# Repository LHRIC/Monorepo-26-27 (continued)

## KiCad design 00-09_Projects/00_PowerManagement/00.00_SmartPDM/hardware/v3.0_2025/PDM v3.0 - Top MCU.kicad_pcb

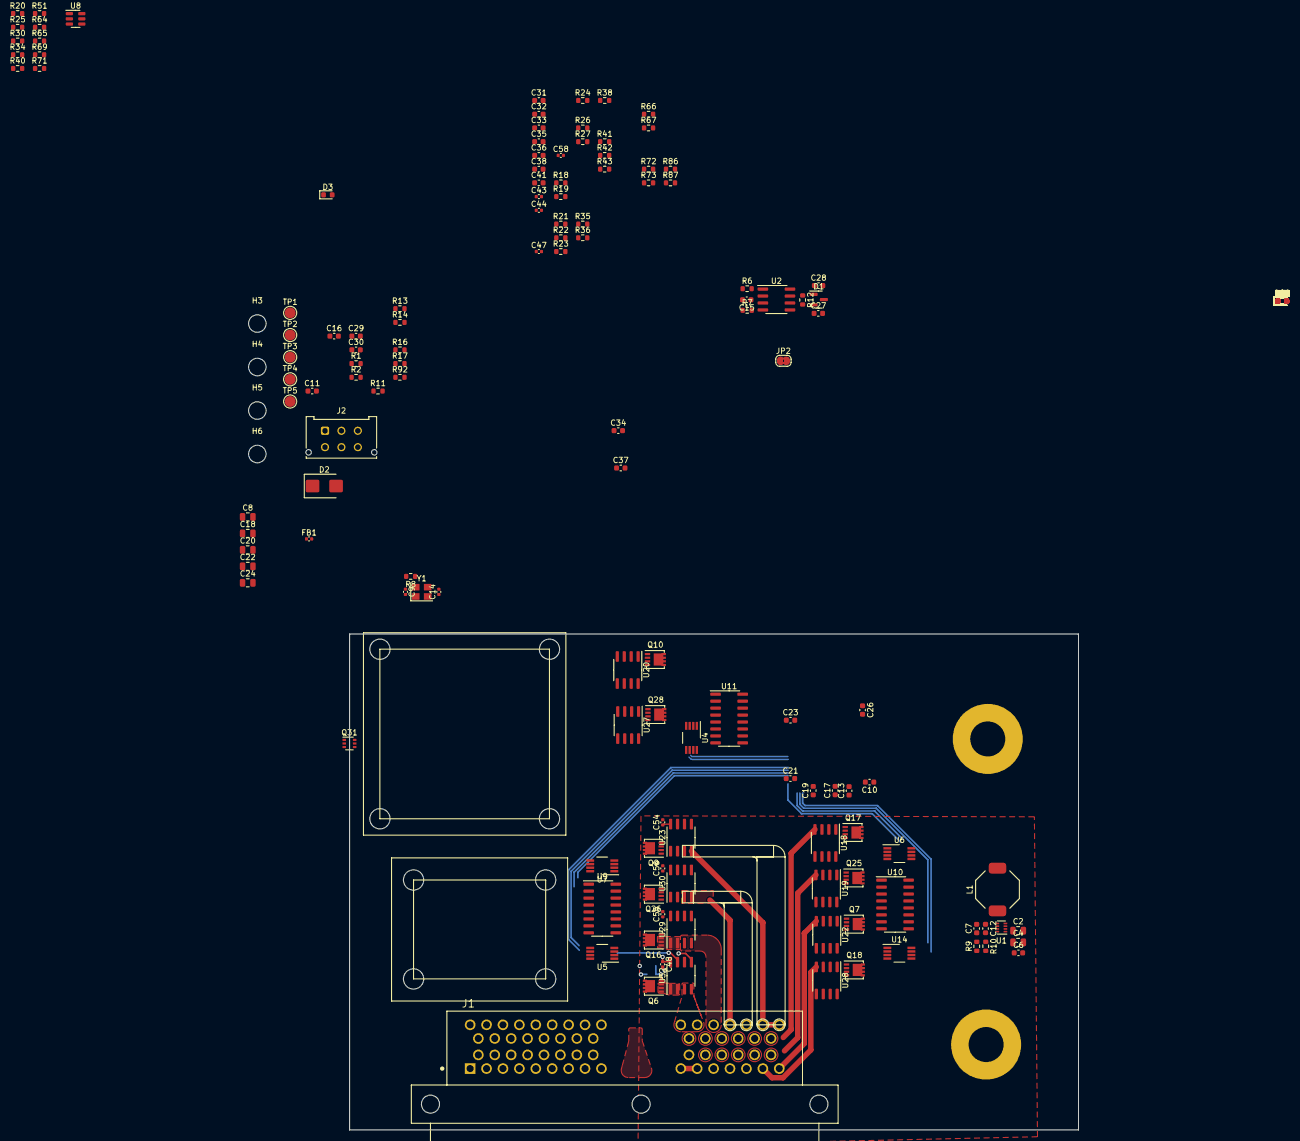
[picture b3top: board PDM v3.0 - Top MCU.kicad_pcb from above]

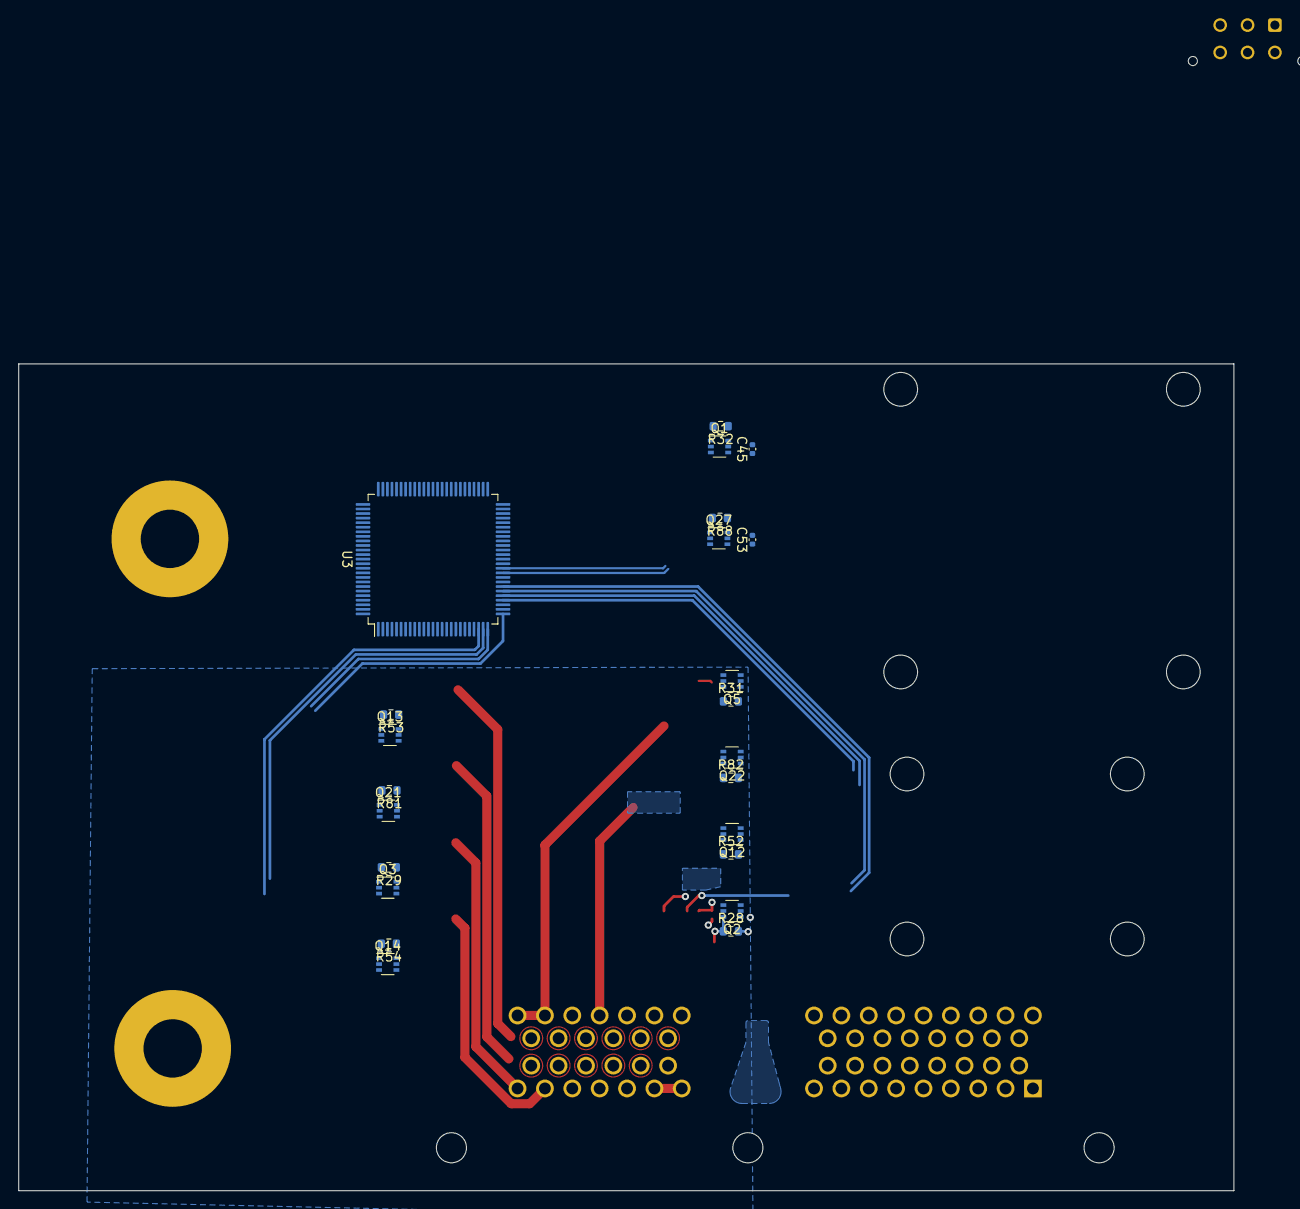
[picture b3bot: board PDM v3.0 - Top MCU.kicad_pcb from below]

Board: 4 copper layers, 133.2 x 90.6 mm, 210 parts (23 on the bottom side), 155 nets.

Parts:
C2, C4: 4.7uF; C_0805_2012Metric
C6, C12, C31, C32, C33, C34, C35, C36, C37, C38, C41: .1uF; C_0603_1608Metric
C7: 33nF; C_0603_1608Metric
C8: 10uF; C_0805_2012Metric
C9, C14: 12pF; C_0402_1005Metric
C10, C11, C13, C15, C17, C19, C21, C23, C26: 0.1uF; C_0603_1608Metric
C16: 1uF; C_0603_1608Metric
C18: C_Small; C_0805_2012Metric
C20, C22, C24: 22uF; C_0805_2012Metric
C27, C28: 100pF; C_0603_1608Metric
C29, C30: 2.2uF; C_0603_1608Metric
C43, C44, C45, C47, C48, C53, C54, C55, C56, C58: .1uF; C_0402_1005Metric
D1: D_TVS_Dual_AAC; SOT-23
D2: 33.2v; D_SMB
D3, D4, D6, D8, D10, D12, D14, D16, D18, D20, D22: RED; LED_0603_1608Metric
D5, D7, D9, D11, D13, D15, D17, D19, D21, D23: GREEN; LED_0603_1608Metric
FB1: 100 @ 100MHz; C_0402_1005Metric
H1, H2: SurLok; SurLok_5.7
H3, H4, H5, H6: Hole; MountingHole_3.2mm_M3
H7, H8, H9, H10, H11, H12, H13, H14: Hole; MountingHole_3.7mm
J1: Conn_02x30; TE_6473427-1
J2: Conn_02x03_Odd_Even; Molex_Micro-Fit_3.0_43045-0612_2x03_P3.00mm_Vertical
JP2: Jumper_2_Bridged; SolderJumper-2_P1.3mm_Bridged2Bar_RoundedPad1.0x1.5mm
L1: 4.7uH; SRU8043-4R7Y
Q1, Q2, Q3, Q5, Q12, Q13, Q14, Q21, Q22, Q27: DMN63D8LDW; SOT-363_SC-70-6
Q6, Q7, Q9, Q10, Q16, Q17, Q18, Q25, Q26, Q28: SiS443DN; Vishay_PowerPAK_1212-8_Single
Q31: BSD235C; SOT-363_SC-70-6
R1: 16k; R_0603_1608Metric
R2: 3.9k; R_0603_1608Metric
R6, R7: 1k; R_0603_1608Metric
R8: 220; R_0603_1608Metric
R9: 30.9k; R_0603_1608Metric
R10, R13, R14, R17, R92: 10k; R_0603_1608Metric
R11, R18, R19, R20, R21, R22, R23, R24, R25, R26, R27, R30, R34, R35, R36, R38, R40, R41, R42, R43, R51, R64, R65, R66, R67, R69, R71, R72, R73, R86, R87: R_Small; R_0603_1608Metric
R12: 120; R_0603_1608Metric
R16, R33, R37, R39, R44, R45, R46, R47, R48, R49, R50, R55, R56, R57, R58, R59, R60, R61, R62, R63, R68: 330; R_0603_1608Metric
R28, R29, R31, R32, R52, R53, R54, R81, R82, R88: 100k; R_0603_1608Metric
TP1, TP2, TP3, TP4, TP5: TP; TestPoint_Pad_D2.0mm
U1: TPS62933; SOT-583
U2: SN65HVD230; SOIC-8_3.9x4.9mm_P1.27mm
U3: STM32F407VETx; LQFP-100_14x14mm_P0.5mm
U4, U5, U6, U7, U14: TLV7012DGKR; VSSOP-8_3.0x3.0mm_P0.65mm
U8: MAX6817EUT+T; SOT-23-6
U9, U10, U11: MC14043B; SOIC-16_3.9x9.9mm_P1.27mm
U18, U19, U20, U22, U23, U27, U28, U29, U30, U32: TMCS1108A3UQDR; SOIC-8_3.9x4.9mm_P1.27mm
Y1: 16MHz; Crystal_SMD_3225-4Pin_3.2x2.5mm

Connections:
+3.3VA: C11.1, C16.1, FB1.2, TP3.1, U3.21 (VREF+), U3.22 (VDDA)
+3V3: C8.1, C10.1, C13.1, C15.1, C17.1, C19.1, C20.1, C21.1, C22.1, C23.1, C24.1, C26.1, C31.1, C32.1, C33.1, C34.1, C35.1, C36.1, C37.1, C38.1, C41.1, C43.1, C44.1, C45.1, C47.1, C48.1, C53.1, C54.1, C55.1, C56.1, C58.1, FB1.1, J2.2, L1.2, R9.1, R13.1, R14.1, R16.1, R18.2, R19.2, R20.2, R21.2, R22.2, R25.2, R30.2, R34.2, R35.2, R36.2, R38.2, R40.2, R51.2, R64.2, R65.2, R66.2, R67.2, R69.2, R71.2, R86.2, R92.1, TP4.1, U2.3 (VCC), U3.6 (VBAT), U3.11 (VDD), U3.19 (VDD), U3.28 (VDD), U3.50 (VDD), U3.75 (VDD), U3.100 (VDD), U4.8 (V+), U5.8 (V+), U6.8 (V+), U7.8 (V+), U8.5 (VCC), U9.5 (Enable), U9.16 (V+), U10.5 (Enable), U10.16 (V+), U11.5 (Enable), U11.16 (V+), U14.8 (V+), U18.8 (VS), U19.8 (VS), U20.8 (VS), U22.8 (VS), U23.8 (VS), U27.8 (VS), U28.8 (VS), U29.8 (VS), U30.8 (VS), U32.8 (VS)
+12V: C2.1, C4.1, C6.1, C18.1, D2.2 (A2), H1.1, Q6.5 (D), Q7.5 (D), Q9.5 (D), Q10.5 (D), Q16.5 (D), Q17.5 (D), Q18.5 (D), Q25.5 (D), Q26.5 (D), Q28.5 (D), R1.1, R28.2, R29.2, R31.2, R32.2, R52.2, R53.2, R54.2, R81.2, R82.2, R88.2, TP1.1, U1.3 (VIN)
BSPD Switch: C18.2, R11.1
CAN_H: C27.1, D1.2 (A2), J1.26, R12.1, U2.7 (CANH)
CAN_L: C28.1, D1.1 (A1), J1.27, R12.2, U2.6 (CANL)
CAN_RX: R7.1, U3.70 (PA11)
CAN_SLEEP: U2.8 (Rs), U3.2 (PE3)
CAN_TX: R6.1, U3.71 (PA12)
CH1_CS: U3.32 (PA7), U5.6 (-), U32.7 (VOUT)
CH1_EN: Q2.2 (G), R20.1, U3.62 (PD15)
CH1_Fault: Q2.5 (G), U3.33 (PC4), U9.2 (Q)
CH1_OUT: J1.54, J1.55, U32.3 (IN-), U32.4 (IN-)
CH1_R: U3.51 (PB12), U9.4 (S)
CH2_CS: U3.31 (PA6), U5.2 (-), U29.7 (VOUT)
CH2_EN: Q12.2 (G), R40.1, U3.63 (PC6)
CH2_Fault: Q12.5 (G), U3.34 (PC5), U9.9 (Q)
CH2_OUT: J1.56, U29.3 (IN-), U29.4 (IN-)
CH2_R: U3.52 (PB13), U9.6 (S)
CH3_CS: U3.30 (PA5), U7.3 (+), U30.7 (VOUT)
CH3_EN: Q22.2 (G), R51.1, U3.64 (PC7)
CH3_Fault: Q22.5 (G), U3.37 (PB2), U9.1 (Q)
CH3_OUT: J1.57, J1.58, U30.3 (IN-), U30.4 (IN-)
CH3_R: U3.53 (PB14), U9.14 (S)
CH4_CS: U3.29 (PA4), U7.6 (-), U23.7 (VOUT)
CH4_EN: Q5.2 (G), R71.1, U3.65 (PC8)
CH4_Fault: Q5.5 (G), U3.38 (PE7), U9.10 (Q)
CH4_OUT: J1.59, J1.60, U23.3 (IN-), U23.4 (IN-)
CH4_R: U3.54 (PB15), U9.12 (S)
CH5_CS: U3.26 (PA3), U14.3 (+), U18.7 (VOUT)
CH5_EN: Q13.2 (G), R25.1, U3.66 (PC9)
CH5_Fault: Q13.5 (G), U3.39 (PE8), U10.2 (Q)
CH5_OUT: J1.53, U18.3 (IN-), U18.4 (IN-)
CH5_R: U3.55 (PD8), U10.4 (S)
CH6_CS: U3.25 (PA2), U14.6 (-), U19.7 (VOUT)
CH6_EN: Q21.2 (G), R34.1, U3.67 (PA8)
CH6_Fault: Q21.5 (G), U3.40 (PE9), U10.9 (Q)
CH6_OUT: J1.47, U19.3 (IN-), U19.4 (IN-)
CH6_R: U3.56 (PD9), U10.6 (S)
CH7_CS: U3.24 (PA1), U6.3 (+), U22.7 (VOUT)
CH7_EN: Q3.2 (G), R64.1, U3.68 (PA9)
CH7_Fault: Q3.5 (G), U3.41 (PE10), U10.10 (Q)
CH7_OUT: J1.41, U22.3 (IN-), U22.4 (IN-)
CH7_R: U3.57 (PD10), U10.12 (S)
CH8_CS: U3.23 (PA0), U6.5 (+), U28.7 (VOUT)
CH8_EN: Q14.2 (G), R69.1, U3.69 (PA10)
CH8_Fault: Q14.5 (G), U3.42 (PE11), U10.1 (Q)
CH8_OUT: J1.40, U28.3 (IN-), U28.4 (IN-)
CH8_R: U3.58 (PD11), U10.14 (S)
CH9_CS: U3.35 (PB0), U4.3 (+), U20.7 (VOUT)
CH9_EN: Q1.2 (G), R30.1, U3.46 (PE15)
CH9_Fault: Q1.5 (G), U3.43 (PE12), U11.2 (Q)
CH9_OUT: U20.3 (IN-), U20.4 (IN-)
CH9_R: U3.59 (PD12), U11.4 (S)
CH10_CS: U3.36 (PB1), U4.6 (-), U27.7 (VOUT)
CH10_EN: Q27.2 (G), R65.1, U3.47 (PB10)
CH10_Fault: Q27.5 (G), U3.44 (PE13), U11.9 (Q)
CH10_OUT: U27.3 (IN-), U27.4 (IN-)
CH10_R: U3.60 (PD13), U11.6 (S)
GND: C2.2, C4.2, C6.2, C7.2, C8.2, C9.1, C10.2, C11.2, C13.2, C14.1, C15.2, C16.2, C17.2, C19.2, C20.2, C21.2, C22.2, C23.2, C24.2, C26.2, C27.2, C28.2, C29.1, C30.1, C31.2, C32.2, C33.2, C34.2, C35.2, C36.2, C37.2, C38.2, C41.2, C43.2, C44.2, C45.2, C47.2, C48.2, C53.2, C54.2, C55.2, C56.2, C58.2, D1.3 (common), D2.1 (A1), D3.1 (K), D4.1 (K), D5.1 (K), D6.1 (K), D7.1 (K), D8.1 (K), D9.1 (K), D10.1 (K), D11.1 (K), D12.1 (K), D13.1 (K), D14.1 (K), D15.1 (K), D16.1 (K), D17.1 (K), D18.1 (K), D19.1 (K), D20.1 (K), D21.1 (K), D22.1 (K), D23.1 (K), H2.1, J1.37, J1.38, J1.39, J1.43, J1.44, J1.45, J1.46, J1.49, J1.50, J1.51, J1.52, J2.5, JP2.2 (B), Q1.1 (S), Q2.1 (S), Q3.1 (S), Q5.1 (S), Q12.1 (S), Q13.1 (S), Q14.1 (S), Q21.1 (S), Q22.1 (S), Q27.1 (S), Q31.1 (SN), Q31.3 (DP), R2.2, R10.2, R11.2, R17.1, R23.2, R24.2, R26.2, R27.2, R41.2, R42.2, R43.2, R72.2, R73.2, R87.2, TP2.1, TP5.1, U1.4 (GND), U2.2 (GND), U3.10 (VSS), U3.20 (VSSA), U3.27 (VSS), U3.74 (VSS), U3.99 (VSS), U4.4 (V-), U5.4 (V-), U6.4 (V-), U7.4 (V-), U8.2 (GND), U9.8 (V-), U10.8 (V-), U11.8 (V-), U14.4 (V-), U18.5 (GND), U19.5 (GND), U20.5 (GND), U22.5 (GND), U23.5 (GND), U27.5 (GND), U28.5 (GND), U29.5 (GND), U30.5 (GND), U32.5 (GND), Y1.2, Y1.4
HSE_IN: C9.2, U3.12 (PH0), Y1.1
HSE_OUT: R8.2, U3.13 (PH1)
Key: R13.2, U8.1 (IN1)
Key_DB: U3.16 (PC1), U8.6 (OUT1)
NRST: J2.1, Q31.4 (SP), U3.14 (NRST)
unnamed: C14.2, R8.1, Y1.3
unnamed: D3.2 (A), R16.2
unnamed: D4.2 (A), R33.2
unnamed: D5.2 (A), R37.2
unnamed: D6.2 (A), R39.2
unnamed: D7.2 (A), R44.2
unnamed: D8.2 (A), R45.2
unnamed: D9.2 (A), R46.2
unnamed: D10.2 (A), R47.2
unnamed: D11.2 (A), R48.2
unnamed: D12.2 (A), R49.2
unnamed: D13.2 (A), R50.2
unnamed: D14.2 (A), R55.2
unnamed: D15.2 (A), R56.2
unnamed: D16.2 (A), R57.2
unnamed: D17.2 (A), R58.2
unnamed: D18.2 (A), R59.2
unnamed: D19.2 (A), R60.2
unnamed: D20.2 (A), R61.2
unnamed: D21.2 (A), R62.2
unnamed: D22.2 (A), R63.2
unnamed: D23.2 (A), R68.2
unnamed: J1.10, J1.11, J1.12, J1.13, J1.14, J1.15, J1.16, J1.17
unnamed: J1.18, J1.19, J1.20, J1.21, J1.22, J1.23, J1.24, J1.25
unnamed: Q1.3 (D), Q1.4 (S)
unnamed: Q2.6 (D), Q6.4 (G), R28.1
unnamed: Q2.3 (D), Q2.4 (S)
unnamed: Q3.6 (D), Q7.4 (G), R29.1
unnamed: Q3.3 (D), Q3.4 (S)
unnamed: Q5.6 (D), Q9.4 (G), R31.1
unnamed: Q5.3 (D), Q5.4 (S)
unnamed: Q6.1 (S), Q6.2 (S), Q6.3 (S), U32.1 (IN+), U32.2 (IN+)
unnamed: Q7.1 (S), Q7.2 (S), Q7.3 (S), U22.1 (IN+), U22.2 (IN+)
unnamed: Q9.1 (S), Q9.2 (S), Q9.3 (S), U23.1 (IN+), U23.2 (IN+)
unnamed: Q1.6 (D), Q10.4 (G), R32.1
unnamed: Q10.1 (S), Q10.2 (S), Q10.3 (S), U20.1 (IN+), U20.2 (IN+)
unnamed: Q12.6 (D), Q16.4 (G), R52.1
unnamed: Q12.3 (D), Q12.4 (S)
unnamed: Q13.6 (D), Q17.4 (G), R53.1
unnamed: Q13.3 (D), Q13.4 (S)
unnamed: Q14.6 (D), Q18.4 (G), R54.1
unnamed: Q14.3 (D), Q14.4 (S)
unnamed: Q16.1 (S), Q16.2 (S), Q16.3 (S), U29.1 (IN+), U29.2 (IN+)
unnamed: Q17.1 (S), Q17.2 (S), Q17.3 (S), U18.1 (IN+), U18.2 (IN+)
unnamed: Q18.1 (S), Q18.2 (S), Q18.3 (S), U28.1 (IN+), U28.2 (IN+)
unnamed: Q21.6 (D), Q25.4 (G), R81.1
unnamed: Q21.3 (D), Q21.4 (S)
unnamed: Q22.6 (D), Q26.4 (G), R82.1
unnamed: Q22.3 (D), Q22.4 (S)
unnamed: Q25.1 (S), Q25.2 (S), Q25.3 (S), U19.1 (IN+), U19.2 (IN+)
unnamed: Q26.1 (S), Q26.2 (S), Q26.3 (S), U30.1 (IN+), U30.2 (IN+)
unnamed: Q27.6 (D), Q28.4 (G), R88.1
unnamed: Q27.3 (D), Q27.4 (S)
unnamed: Q28.1 (S), Q28.2 (S), Q28.3 (S), U27.1 (IN+), U27.2 (IN+)
unnamed: Q31.5 (GP), Q31.6 (DN), R92.2
unnamed: C12.2, U1.6 (BST)
unnamed: R9.2, R10.1, U1.8 (FB)
unnamed: C7.1, U1.7 (SS)
unnamed: C12.1, L1.1, U1.5 (SW)
unnamed: R6.2, U2.1 (D)
unnamed: R7.2, U2.4 (R)
unnamed: R17.2, U3.94 (BOOT0)
unnamed: C29.2, U3.49 (VCAP_1)
unnamed: C30.2, U3.73 (VCAP_2)
unnamed: R22.1, R27.1, U4.2 (-)
unnamed: R86.1, R87.1, U4.5 (+)
unnamed: R35.1, R41.1, U5.3 (+)
unnamed: R38.1, R43.1, U5.5 (+)
unnamed: R19.1, R24.1, U6.2 (-)
unnamed: R18.1, R23.1, U6.6 (-)
unnamed: R67.1, R73.1, U7.2 (-)
unnamed: R21.1, R26.1, U7.5 (+)
unnamed: U5.7, U9.3 (R)
unnamed: U5.1, U9.7 (R)
unnamed: U7.7, U9.11 (R)
unnamed: U7.1, U9.15 (R)
unnamed: U10.3 (R), U14.1
unnamed: U10.7 (R), U14.7
unnamed: U6.1, U10.11 (R)
unnamed: U6.7, U10.15 (R)
unnamed: U4.1, U11.3 (R)
unnamed: U4.7, U11.7 (R)
unnamed: R36.1, R42.1, U14.2 (-)
unnamed: R66.1, R72.1, U14.5 (+)
SWCLK: J2.3, U3.76 (PA14)
SWDIO: J2.4, U3.72 (PA13)
SWDN: J1.1, Q31.2 (GN)
SWO: J2.6, U3.89 (PB3)
Starter: J1.35, J1.36, R14.2, U8.3 (IN2)
VBAT: R1.2, R2.1, U3.17 (PC2)

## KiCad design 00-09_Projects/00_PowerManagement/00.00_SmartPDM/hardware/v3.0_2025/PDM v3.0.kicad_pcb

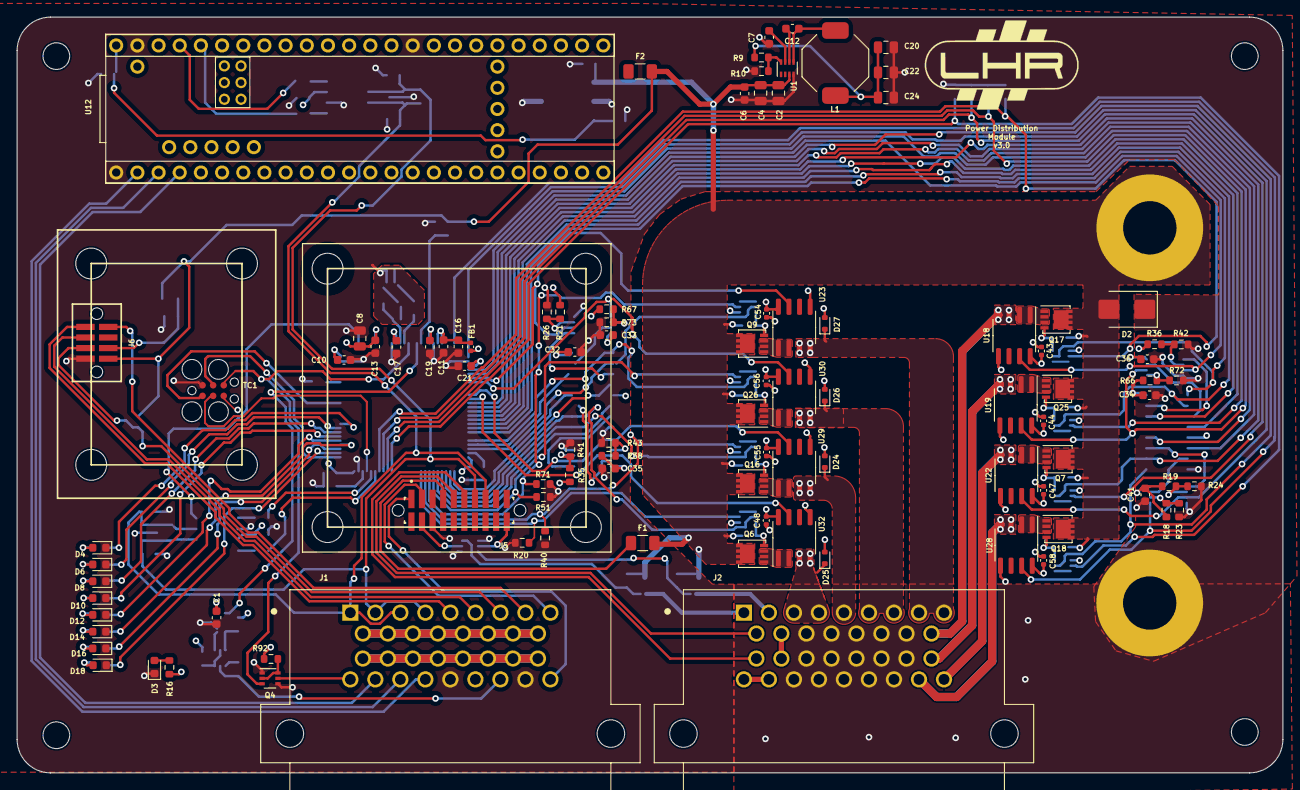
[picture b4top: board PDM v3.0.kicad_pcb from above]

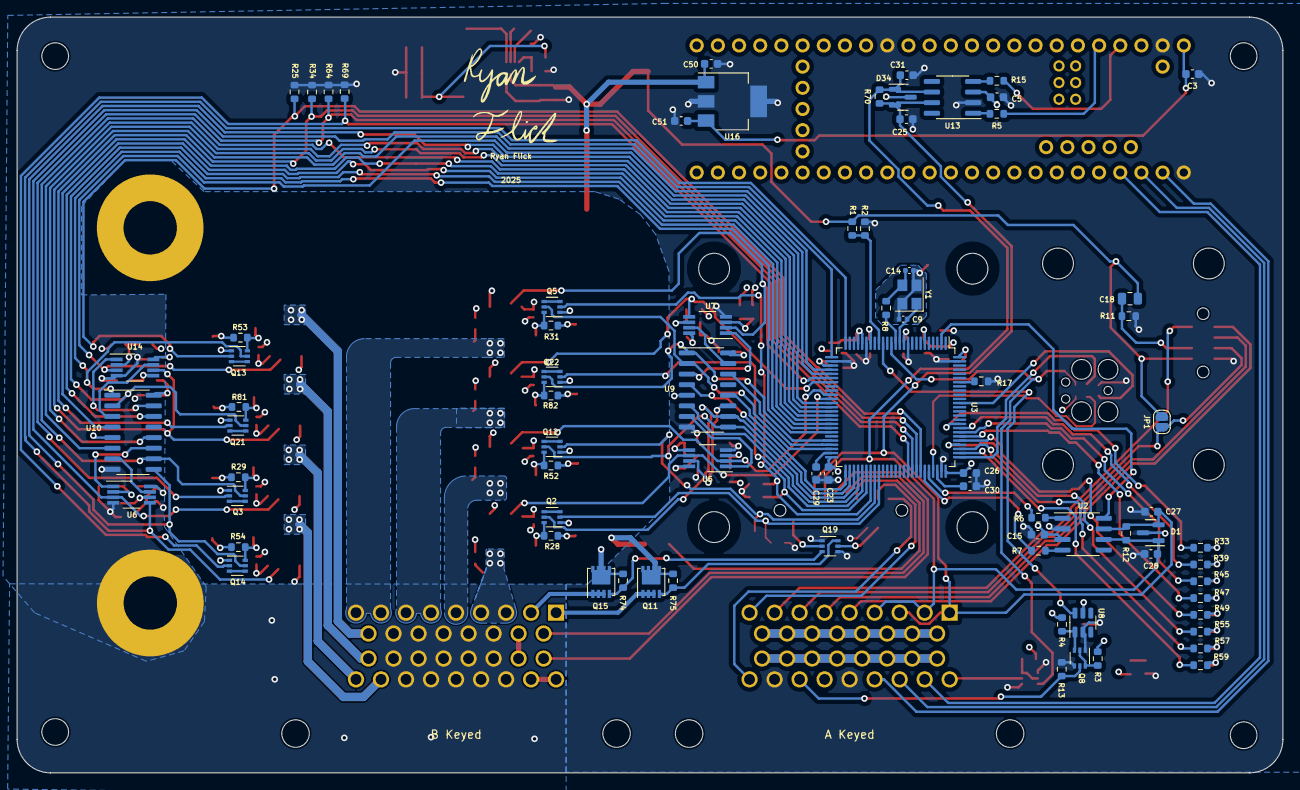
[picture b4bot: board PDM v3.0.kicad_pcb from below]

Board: 4 copper layers, 151.8 x 90.6 mm, 190 parts (79 on the bottom side), 157 nets.

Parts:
C1, C6, C12, C32, C33, C34, C35, C36, C41: .1uF; C_0603_1608Metric
C2, C4: 4.7uF; C_0805_2012Metric
C3, C5, C10, C11, C13, C15, C17, C19, C21, C23, C26, C51: 0.1uF; C_0603_1608Metric
C7: 33nF; C_0603_1608Metric
C8: 10uF; C_0805_2012Metric
C9, C14: 12pF; C_0402_1005Metric
C16: 1uF; C_0603_1608Metric
C18: C_Small; C_0805_2012Metric
C20, C22, C24: 22uF; C_0805_2012Metric
C25, C27, C28, C31: 100pF; C_0603_1608Metric
C29, C30: 2.2uF; C_0603_1608Metric
C43, C44, C47, C48, C54, C55, C56, C58: .1uF; C_0402_1005Metric
C50: 0.22uF; C_0603_1608Metric
D1, D34: D_TVS_Dual_AAC; SOT-23
D2: 33.2v; D_SMB
D3, D4, D6, D8, D10, D12, D14, D16, D18: RED; LED_0603_1608Metric
D24, D25, D26, D27: D_Schottky; D_SOD-523
F1, F2: 750mA; Fuse_1206_3216Metric
FB1: 100 @ 100MHz; C_0402_1005Metric
H1, H2: SurLok; SurLok_5.7
H3, H4, H5, H6: Hole; MountingHole_3.2mm_M3
H7, H8, H9, H10, H11, H12, H13, H14: Hole; MountingHole_3.7mm
J1: Conn_02x17_Counter_Clockwise; TE_6437288-1
J2: Conn_02x17_Counter_Clockwise; TE_6437288-2
J5: Conn_02x10_Odd_Even; SAMTEC_SFM-110-02-L-D-A
J6: Conn_02x04_Odd_Even; SAMTEC-SFM-104-02-X-D-A
JP1: Jumper_2_Open; SolderJumper-2_P1.3mm_Open_RoundedPad1.0x1.5mm
L1: 4.7uH; SRU8043-4R7Y
Q2, Q3, Q4, Q5, Q8, Q12, Q13, Q14, Q19, Q21, Q22: DMN63D8LDW; SOT-363_SC-70-6
Q6, Q7, Q9, Q11, Q15, Q16, Q17, Q18, Q25, Q26: SiS443DN; Vishay_PowerPAK_1212-8_Single
R1: 16k; R_0603_1608Metric
R2: 3.9k; R_0603_1608Metric
R3, R4, R10, R13, R17, R74, R75, R92: 10k; R_0603_1608Metric
R5, R6, R7, R15: 1k; R_0603_1608Metric
R8: 220; R_0603_1608Metric
R9: 30.9k; R_0603_1608Metric
R11, R18, R19, R20, R21, R23, R24, R25, R26, R34, R35, R36, R38, R40, R41, R42, R43, R51, R64, R66, R67, R69, R71, R72, R73: R_Small; R_0603_1608Metric
R12, R70: 120; R_0603_1608Metric
R16, R33, R39, R45, R47, R49, R55, R57, R59: 330; R_0603_1608Metric
R28, R29, R31, R52, R53, R54, R81, R82: 100k; R_0603_1608Metric
TC1: TC2030-IDC
U1: TPS62933; SOT-583
U2, U13: SN65HVD230; SOIC-8_3.9x4.9mm_P1.27mm
U3: STM32F407VETx; LQFP-100_14x14mm_P0.5mm
U5, U6, U7, U14: TLV7012DGKR; VSSOP-8_3.0x3.0mm_P0.65mm
U8: MAX6817EUT+T; SOT-23-6
U9, U10: MC14043B; SOIC-16_3.9x9.9mm_P1.27mm
U12: Teensy 4.1
U16: LM340MP-5.0/NOPB; SOT-223-3_TabPin2
U18, U19, U22, U23, U28, U29, U30, U32: TMCS1108A3UQDR; SOIC-8_3.9x4.9mm_P1.27mm
Y1: 16MHz; Crystal_SMD_3225-4Pin_3.2x2.5mm

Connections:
+3.3VA: C11.1, C16.1, FB1.2, U3.21 (VREF+), U3.22 (VDDA)
+3V3: C1.1, C5.1, C8.1, C10.1, C13.1, C15.1, C17.1, C19.1, C20.1, C21.1, C22.1, C23.1, C24.1, C26.1, C32.1, C33.1, C34.1, C35.1, C36.1, C41.1, C43.1, C44.1, C47.1, C48.1, C54.1, C55.1, C56.1, C58.1, FB1.1, J1.31, L1.2, R3.1, R4.1, R9.1, R16.1, R18.2, R19.2, R21.2, R35.2, R36.2, R38.2, R66.2, R67.2, R92.1, TC1.5, U2.3 (VCC), U3.6 (VBAT), U3.11 (VDD), U3.19 (VDD), U3.28 (VDD), U3.50 (VDD), U3.75 (VDD), U3.100 (VDD), U5.8 (V+), U6.8 (V+), U7.8 (V+), U8.5 (VCC), U9.5 (Enable), U9.16 (V+), U10.5 (Enable), U10.16 (V+), U13.3 (VCC), U14.8 (V+), U18.8 (VS), U19.8 (VS), U22.8 (VS), U23.8 (VS), U28.8 (VS), U29.8 (VS), U30.8 (VS), U32.8 (VS)
+5V: C3.2, C51.2, U12.45 (Vin), U16.3 (VO)
+6V: J2.11, J2.19
+12V: C2.1, C4.1, C6.1, C18.1, C50.2, D2.2 (A2), F1.2, F2.2, H1.1, J6.2, JP1.2 (B), Q6.5 (D), Q7.5 (D), Q9.5 (D), Q11.5 (D), Q15.5 (D), Q16.5 (D), Q17.5 (D), Q18.5 (D), Q25.5 (D), Q26.5 (D), R1.1, R28.2, R29.2, R31.2, R52.2, R53.2, R54.2, R74.2, R75.2, R81.2, R82.2, U1.3 (VIN), U16.1 (VI)
BSPD Switch: C18.2, J6.4, R11.1
Brake: J1.5, J6.7
CAN_H: C25.1, C27.1, D1.2 (A2), D34.2 (A2), J1.1, J1.3, J5.15, R12.1, R70.1, U2.7 (CANH), U13.7 (CANH)
CAN_L: C28.1, C31.1, D1.1 (A1), D34.1 (A1), J1.2, J1.4, J5.13, R12.2, R70.2, U2.6 (CANL), U13.6 (CANL)
CAN_RX: R7.1, U3.70 (PA11)
CAN_SLEEP: U2.8 (Rs), U3.2 (PE3)
CAN_TX: R6.1, U3.71 (PA12)
CH1_CS: U3.36 (PB1), U5.6 (-), U32.7 (VOUT)
CH1_EN: Q2.2 (G), R20.2, U3.59 (PD12)
CH1_Fault: Q2.5 (G), U3.53 (PB14), U9.10 (Q)
CH1_OUT: D25.1 (K), J2.3, J2.4, U32.3 (IN-), U32.4 (IN-)
CH1_R: U3.51 (PB12), U9.12 (S)
CH1_RED: R33.1, U3.84 (PD3)
CH2_CS: U3.35 (PB0), U5.2 (-), U29.7 (VOUT)
CH2_EN: Q12.2 (G), R40.2, U3.58 (PD11)
CH2_Fault: Q12.5 (G), U3.54 (PB15), U9.9 (Q)
CH2_OUT: D24.1 (K), J2.5, U29.3 (IN-), U29.4 (IN-)
CH2_R: U3.55 (PD8), U9.6 (S)
CH2_RED: R39.1, U3.83 (PD2)
CH3_CS: U3.32 (PA7), U7.5 (+), U30.7 (VOUT)
CH3_EN: Q22.2 (G), R51.2, U3.56 (PD9)
CH3_Fault: Q22.5 (G), U3.46 (PE15), U9.1 (Q)
CH3_OUT: D26.1 (K), J2.6, J2.7, U30.3 (IN-), U30.4 (IN-)
CH3_R: U3.47 (PB10), U9.14 (S)
CH3_RED: R45.1, U3.82 (PD1)
CH4_CS: U3.31 (PA6), U7.2 (-), U23.7 (VOUT)
CH4_EN: Q5.2 (G), R71.2, U3.57 (PD10)
CH4_Fault: Q5.5 (G), U3.48 (PB11), U9.2 (Q)
CH4_OUT: D27.1 (K), J2.8, J2.9, U23.3 (IN-), U23.4 (IN-)
CH4_R: U3.52 (PB13), U9.4 (S)
CH4_RED: R47.1, U3.81 (PD0)
CH5_CS: U3.30 (PA5), U14.3 (+), U18.7 (VOUT)
CH5_EN: Q13.2 (G), R25.2, U3.69 (PA10)
CH5_Fault: Q13.5 (G), U3.44 (PE13), U10.1 (Q)
CH5_OUT: J2.17, U18.3 (IN-), U18.4 (IN-)
CH5_R: U3.42 (PE11), U10.14 (S)
CH5_RED: R49.1, U3.80 (PC12)
CH6_CS: U3.29 (PA4), U14.6 (-), U19.7 (VOUT)
CH6_EN: Q21.2 (G), R34.2, U3.68 (PA9)
CH6_Fault: Q21.5 (G), U3.43 (PE12), U10.2 (Q)
CH6_OUT: J2.25, U19.3 (IN-), U19.4 (IN-)
CH6_R: U3.41 (PE10), U10.4 (S)
CH6_RED: R55.1, U3.79 (PC11)
CH7_CS: U3.26 (PA3), U6.3 (+), U22.7 (VOUT)
CH7_EN: Q3.2 (G), R64.2, U3.67 (PA8)
CH7_Fault: Q3.5 (G), U3.40 (PE9), U10.10 (Q)
CH7_OUT: J2.34, U22.3 (IN-), U22.4 (IN-)
CH7_R: U3.39 (PE8), U10.12 (S)
CH7_RED: R57.1, U3.78 (PC10)
CH8_CS: U3.25 (PA2), U6.5 (+), U28.7 (VOUT)
CH8_EN: Q14.2 (G), R69.2, U3.66 (PC9)
CH8_Fault: Q14.5 (G), U3.37 (PB2), U10.9 (Q)
CH8_OUT: J2.33, U28.3 (IN-), U28.4 (IN-)
CH8_R: U3.38 (PE7), U10.6 (S)
CH8_RED: R59.1, U3.77 (PA15)
CH9_OUT: F1.1, J5.7
DOWNSHIFT: J5.20, Q19.2 (G)
DOWNSHIFT_BUTTON: J1.34, J5.1
Data Log: J1.27, U12.2
ECU Disc: J1.6, J6.5
ECU_DOWNSHIFT: J2.10, J5.9
ECU_UPSHIFT: J2.18, J5.11
GND: C1.2, C2.2, C3.1, C4.2, C5.2, C6.2, C7.2, C8.2, C9.1, C10.2, C11.2, C13.2, C14.1, C15.2, C16.2, C17.2, C19.2, C20.2, C21.2, C22.2, C23.2, C24.2, C25.2, C26.2, C27.2, C28.2, C29.1, C30.1, C31.2, C32.2, C33.2, C34.2, C35.2, C36.2, C41.2, C43.2, C44.2, C47.2, C48.2, C50.1, C51.1, C54.2, C55.2, C56.2, C58.2, D1.3 (common), D2.1 (A1), D3.1 (K), D4.1 (K), D6.1 (K), D8.1 (K), D10.1 (K), D12.1 (K), D14.1 (K), D16.1 (K), D18.1 (K), D24.2 (A), D25.2 (A), D26.2 (A), D27.2 (A), D34.3 (common), H2.1, J1.30, J1.33, J2.12, J2.13, J2.14, J2.15, J2.16, J2.20, J2.21, J2.22, J2.23, J2.24, J2.28, J2.29, J2.30, J2.31, J2.32, J5.6, J6.1, Q2.1 (S), Q3.1 (S), Q4.1 (S), Q4.4 (S), Q5.1 (S), Q8.1 (S), Q8.4 (S), Q12.1 (S), Q13.1 (S), Q14.1 (S), Q19.1 (S), Q19.4 (S), Q21.1 (S), Q22.1 (S), R2.2, R10.2, R11.2, R13.1, R17.1, R20.1, R23.2, R24.2, R25.1, R26.2, R34.1, R40.1, R41.2, R42.2, R43.2, R51.1, R64.1, R69.1, R71.1, R72.2, R73.2, TC1.2, U1.4 (GND), U2.2 (GND), U3.10 (VSS), U3.20 (VSSA), U3.27 (VSS), U3.74 (VSS), U3.99 (VSS), U5.4 (V-), U6.4 (V-), U7.4 (V-), U8.2 (GND), U9.8 (V-), U10.8 (V-), U12.42 (GND), U12.43 (GND), U12.44 (GND), U13.2 (GND), U14.4 (V-), U16.2 (GND), U18.5 (GND), U19.5 (GND), U22.5 (GND), U23.5 (GND), U28.5 (GND), U29.5 (GND), U30.5 (GND), U32.5 (GND), Y1.2, Y1.4
HSE_IN: C9.2, U3.12 (PH0), Y1.1
HSE_OUT: R8.2, U3.13 (PH1)
Key: J1.32, Q8.5 (G), R13.2
Key_3V: Q8.3 (D), R4.2, U8.1 (IN1)
Key_DB: U3.16 (PC1), U8.6 (OUT1)
NRST: Q4.3 (D), TC1.6, U3.14 (NRST)
unnamed: C14.2, R8.1, Y1.3
unnamed: D3.2 (A), R16.2
unnamed: D4.2 (A), R33.2
unnamed: D6.2 (A), R39.2
unnamed: D8.2 (A), R45.2
unnamed: D10.2 (A), R47.2
unnamed: D12.2 (A), R49.2
unnamed: D14.2 (A), R55.2
unnamed: D16.2 (A), R57.2
unnamed: D18.2 (A), R59.2
unnamed: J1.10, J1.11, J1.12, J1.13, J1.14, J1.15, J1.16, J1.17
unnamed: J1.18, J1.19, J1.20, J1.21, J1.22, J1.23, J1.24, J1.25
unnamed: Q2.6 (D), Q6.4 (G), R28.1
unnamed: Q2.3 (D), Q2.4 (S)
unnamed: Q3.6 (D), Q7.4 (G), R29.1
unnamed: Q3.3 (D), Q3.4 (S)
unnamed: Q4.2 (G), Q4.6 (D), R92.2
unnamed: Q5.6 (D), Q9.4 (G), R31.1
unnamed: Q5.3 (D), Q5.4 (S)
unnamed: Q6.1 (S), Q6.2 (S), Q6.3 (S), U32.1 (IN+), U32.2 (IN+)
unnamed: Q7.1 (S), Q7.2 (S), Q7.3 (S), U22.1 (IN+), U22.2 (IN+)
unnamed: Q8.2 (G), Q8.6 (D), R3.2
unnamed: Q9.1 (S), Q9.2 (S), Q9.3 (S), U23.1 (IN+), U23.2 (IN+)
unnamed: Q11.4 (G), Q19.6 (D), R75.1
unnamed: Q12.6 (D), Q16.4 (G), R52.1
unnamed: Q12.3 (D), Q12.4 (S)
unnamed: Q13.6 (D), Q17.4 (G), R53.1
unnamed: Q13.3 (D), Q13.4 (S)
unnamed: Q14.6 (D), Q18.4 (G), R54.1
unnamed: Q14.3 (D), Q14.4 (S)
unnamed: Q15.4 (G), Q19.3 (D), R74.1
unnamed: Q16.1 (S), Q16.2 (S), Q16.3 (S), U29.1 (IN+), U29.2 (IN+)
unnamed: Q17.1 (S), Q17.2 (S), Q17.3 (S), U18.1 (IN+), U18.2 (IN+)
unnamed: Q18.1 (S), Q18.2 (S), Q18.3 (S), U28.1 (IN+), U28.2 (IN+)
unnamed: Q21.6 (D), Q25.4 (G), R81.1
unnamed: Q21.3 (D), Q21.4 (S)
unnamed: Q22.6 (D), Q26.4 (G), R82.1
unnamed: Q22.3 (D), Q22.4 (S)
unnamed: Q25.1 (S), Q25.2 (S), Q25.3 (S), U19.1 (IN+), U19.2 (IN+)
unnamed: Q26.1 (S), Q26.2 (S), Q26.3 (S), U30.1 (IN+), U30.2 (IN+)
unnamed: C12.2, U1.6 (BST)
unnamed: R9.2, R10.1, U1.8 (FB)
unnamed: C7.1, U1.7 (SS)
unnamed: C12.1, L1.1, U1.5 (SW)
unnamed: R6.2, U2.1 (D)
unnamed: R7.2, U2.4 (R)
unnamed: R17.2, U3.94 (BOOT0)
unnamed: C29.2, U3.49 (VCAP_1)
unnamed: C30.2, U3.73 (VCAP_2)
unnamed: R35.1, R41.1, U5.3 (+)
unnamed: R38.1, R43.1, U5.5 (+)
unnamed: R19.1, R24.1, U6.2 (-)
unnamed: R18.1, R23.1, U6.6 (-)
unnamed: R21.1, R26.1, U7.3 (+)
unnamed: R67.1, R73.1, U7.6 (-)
unnamed: U7.1, U9.3 (R)
unnamed: U5.1, U9.7 (R)
unnamed: U5.7, U9.11 (R)
unnamed: U7.7, U9.15 (R)
unnamed: U10.3 (R), U14.7
unnamed: U6.7, U10.7 (R)
unnamed: U6.1, U10.11 (R)
unnamed: U10.15 (R), U14.1
unnamed: R5.2, U13.1 (D)
unnamed: R15.2, U13.4 (R)
unnamed: R36.1, R42.1, U14.2 (-)
unnamed: R66.1, R72.1, U14.5 (+)
Radio RX: J1.29, U12.0
Radio TX: J1.28, U12.1
Relay Output: J1.7, J6.3, JP1.1 (A)
SWCLK: TC1.4, U3.76 (PA14)
SWDIO: TC1.3, U3.72 (PA13)
SWDN: J1.26, Q4.5 (G)
SWO: TC1.1, U3.89 (PB3)
Solenoid D: J2.2, Q15.1 (S), Q15.2 (S), Q15.3 (S)
Solenoid U: J2.1, Q11.1 (S), Q11.2 (S), Q11.3 (S)
Starter: J2.26, J2.27
TPS: J1.8, J6.8
Teensy CAN RX: R15.1, U12.23
Teensy CAN TX: R5.1, U12.22
UPSHIFT: J5.4, Q19.5 (G)
UPSHIFT_BUTTON: J1.9, J5.3
VBAT: R1.2, R2.1, U3.17 (PC2)
